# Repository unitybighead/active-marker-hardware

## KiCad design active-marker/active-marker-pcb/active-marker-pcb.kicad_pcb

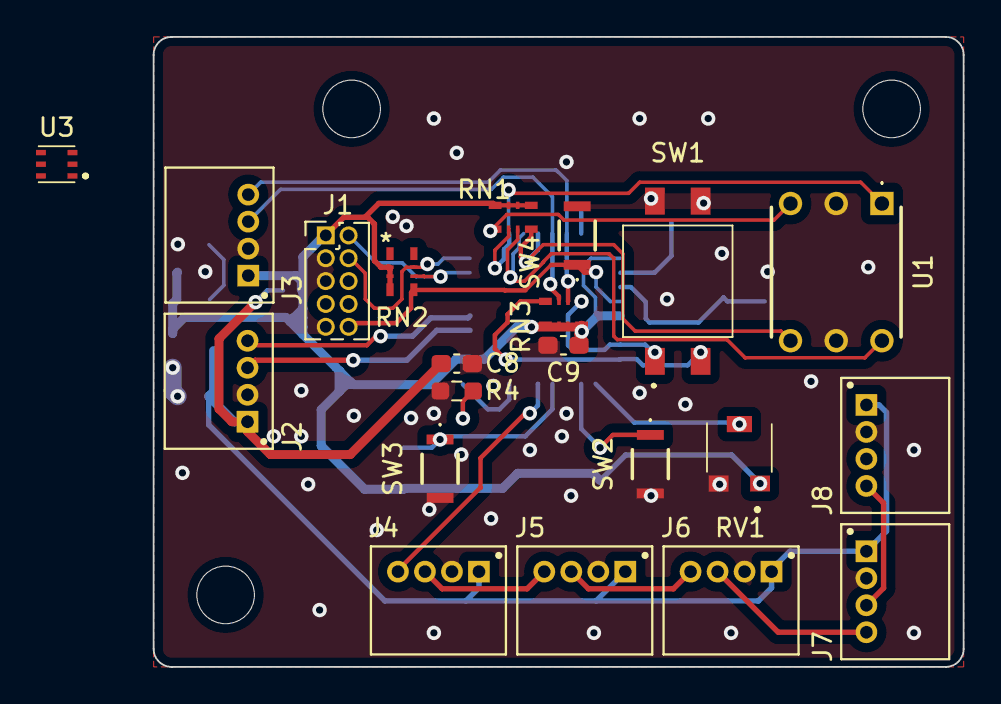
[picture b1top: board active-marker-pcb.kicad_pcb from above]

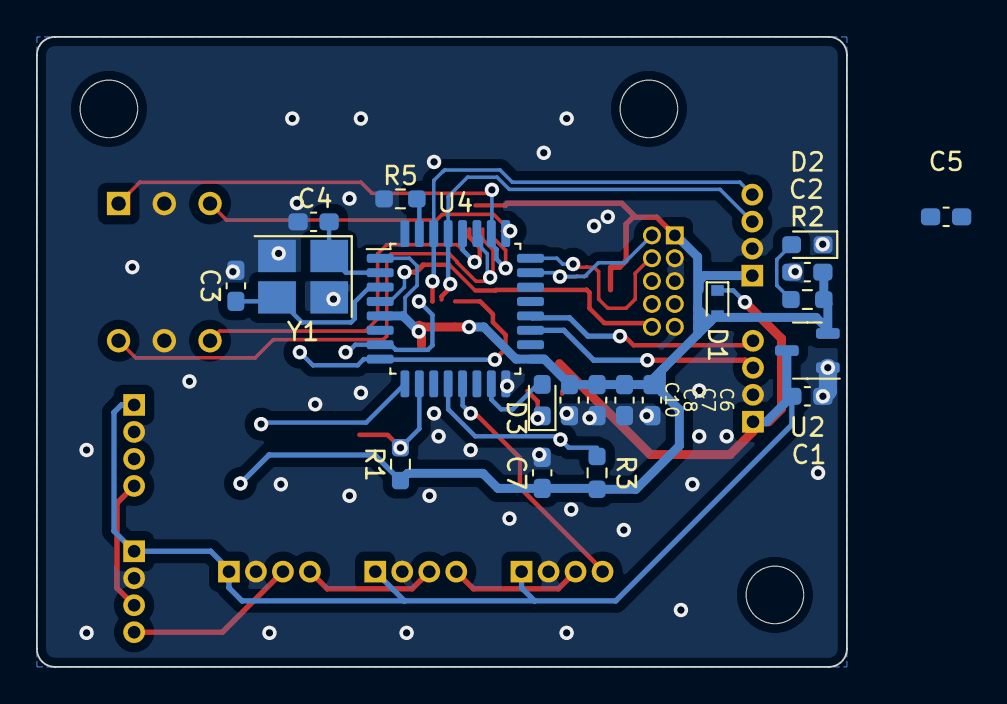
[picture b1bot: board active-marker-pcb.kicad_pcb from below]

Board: 2 copper layers, 45.0 x 35.0 mm, 44 parts (20 on the bottom side), 30 nets.

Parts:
C1, C7#2: 1u; C_0603_1608Metric_Pad1.08x0.95mm_HandSolder
C2: 10u; C_0603_1608Metric_Pad1.08x0.95mm_HandSolder
C3, C4: 15p; C_0603_1608Metric_Pad1.08x0.95mm_HandSolder
C5, C7, C8: 0.1u; C_0603_1608Metric_Pad1.08x0.95mm_HandSolder
C6: 4.7u; C_0603_1608Metric_Pad1.08x0.95mm_HandSolder
C8#2, C9: 100n; C_0603_1608Metric_Pad1.08x0.95mm_HandSolder
C10: 10n; C_0603_1608Metric_Pad1.08x0.95mm_HandSolder
D1: D_Schottky; D_SOD-523
D2: Power; LED_0603_1608Metric_Pad1.05x0.95mm_HandSolder
D3: LED_Small; LED_0603_1608Metric_Pad1.05x0.95mm_HandSolder
H1, H2, H3: MountingHole; MountingHole_3.2mm_M3_ISO7380
J1: Conn_01x10; PinHeader_2x05_P1.27mm_Vertical
J2, J3, J4, J5, J6, J7, J8: Conn_01x04; JST_S4B-ZR_LF__SN_
R1, R3, R5: 10k; R_0603_1608Metric_Pad0.98x0.95mm_HandSolder
R2, R4: 1k; R_0603_1608Metric_Pad0.98x0.95mm_HandSolder
RN1, RN2, RN3: 10k; BO_CAY10_PAN-L
RV1: 10k; PVG3A202C01R00
SW1: SW_DIP_x02; DS04254202BKSMT
SW2, SW3, SW4: SW_Push; EVP6AWD40
U1: 220ADA16
U2: XC6206PxxxMR; SOT-23-3
U3: VEML6030
U4: STM32F303K8Tx; LQFP-32_7x7mm_P0.8mm
Y1: NX3225GA-32M; Crystal_SMD_3225-4Pin_3.2x2.5mm_HandSoldering

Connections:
+3V3: C2.1, C5.1, C6.1, C7.1, C7#2.1, C8#2.1, C9.1, C10.1, D1.2 (A), J1.1, J3.4, R1.1, R2.1, R3.1, RN1.1 (R1.1), RN1.3 (R2.1), RN1.5 (R3.1), RN1.7 (R4.1), RN2.3 (R2.1), RN2.5 (R3.1), RN2.7 (R4.1), RN3.1 (R1.1), RN3.3 (R2.1), RN3.5 (R3.1), RN3.7 (R4.1), RV1.1, U2.2 (VO), U3.4 (ADD), U3.6 (VDD), U4.1 (VDD), U4.5 (VDDA), U4.17 (VDD)
+5V: C1.1, C8.1, D1.1 (K), J2.4, J4.4, J5.4, J6.4, J7.4, J8.4, U2.3 (VI)
/D12: J4.2, J5.1
/D23: J5.2, J6.1
/D34: J6.2, J7.1
/D45: J7.2, J8.1
/I2C_SCL: J3.2, RN3.4 (R2.2), U3.5 (SCL), U4.29 (PB6)
/I2C_SDA: J3.1, RN3.6 (R3.2), U3.2 (SDA), U4.30 (PB7)
/ID1: RN1.6 (R3.2), U1.1, U4.26 (PB3)
/ID2: RN1.2 (R1.2), U1.2, U4.28 (PB5)
/ID4: RN1.8 (R4.2), U1.4, U4.25 (PA15)
/ID8: RN1.4 (R2.2), U1.8, U4.27 (PB4)
/OSC_IN: C4.1, U4.2 (PF0), Y1.1
/OSC_OUT: C3.1, U4.3 (PF1), Y1.3
/SPI_MOSI: J4.1, U4.13 (PA7)
/SWCLK: J1.4, RN2.4 (R2.2), U4.24 (PA14)
/SWDIO: J1.2, RN2.6 (R3.2), U4.23 (PA13)
/UART_RX: J2.1, U4.20 (PA10)
/UART_TX: J2.2, U4.19 (PA9)
/USER_BUTTON1: R1.2, SW2.1, U4.10 (PA4)
/USER_BUTTON2: R3.2, SW3.1, U4.12 (PA6)
/USER_LED: D3.2 (A), U4.15 (PB1)
/USER_SELECT1: RN3.8 (R4.2), SW1.1, U4.7 (PA1)
/USER_SELECT2: RN3.2 (R1.2), SW1.2, U4.8 (PA2)
/USER_VR: RV1.2, U4.9 (PA3)
/~NRST: J1.10, RN2.8 (R4.2), SW4.1, U4.4 (NRST)
GND: C1.2, C2.2, C3.2, C4.2, C5.2, C6.2, C7.2, C7#2.2, C8.2, C8#2.2, C9.2, C10.2, D2.1 (K), J1.3, J1.5, J1.9, J2.3, J3.3, J4.3, J5.3, J6.3, J7.3, J8.3, R4.2, R5.2, RV1.3, SW1.3, SW1.4, SW2.2, SW3.2, SW4.2, U1.C1, U1.C2, U2.1 (GND), U3.1 (GND), U4.16 (VSS), U4.32 (VSS), Y1.2, Y1.4
unnamed: D2.2 (A), R2.2
unnamed: D3.1 (K), R4.1
unnamed: R5.1, U4.31 (BOOT0)

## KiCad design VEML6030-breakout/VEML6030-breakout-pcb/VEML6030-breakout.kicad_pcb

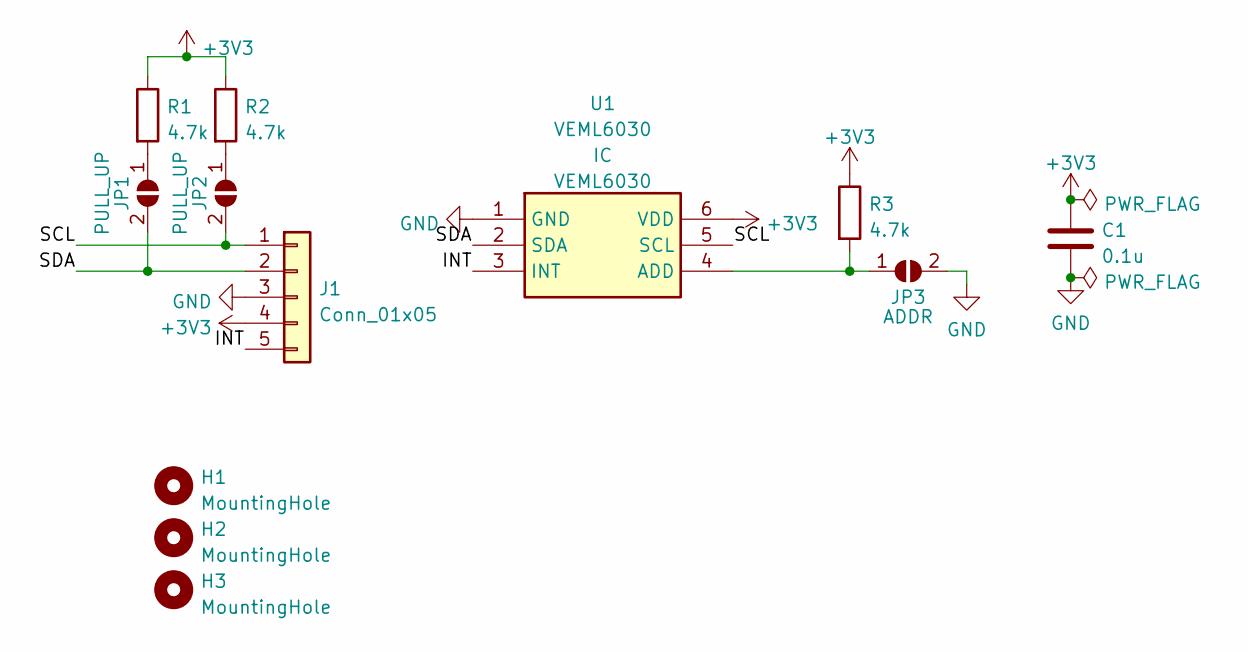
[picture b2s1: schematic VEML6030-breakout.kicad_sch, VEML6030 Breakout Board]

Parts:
C1: 0.1u; C_0603_1608Metric_Pad1.08x0.95mm_HandSolder
H1, H2, H3: MountingHole; MountingHole_3.2mm_M3_ISO7380
J1: Conn_01x05; JST_XH_S5B-XH-A_1x05_P2.50mm_Horizontal
JP1, JP2: PULL_UP; SolderJumper-2_P1.3mm_Open_Pad1.0x1.5mm
JP3: ADDR; SolderJumper-2_P1.3mm_Open_Pad1.0x1.5mm
R1, R2, R3: 4.7k; R_0603_1608Metric_Pad0.98x0.95mm_HandSolder
U1: VEML6030; Mouser Part Number 78-VEML6030

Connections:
+3V3: C1.1, J1.4, R1.1, R2.1, R3.1, U1.6 (VDD)
/INT: J1.5, U1.3 (INT)
/SCL: J1.1, JP2.2 (B), U1.5 (SCL)
/SDA: J1.2, JP1.2 (B), U1.2 (SDA)
GND: C1.2, J1.3, JP3.2 (B), U1.1 (GND)
unnamed: JP1.1 (A), R1.2
unnamed: JP2.1 (A), R2.2
unnamed: JP3.1 (A), R3.2, U1.4 (ADD)

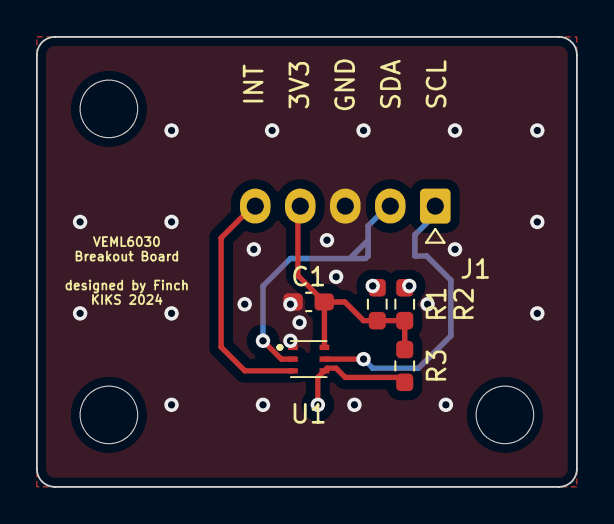
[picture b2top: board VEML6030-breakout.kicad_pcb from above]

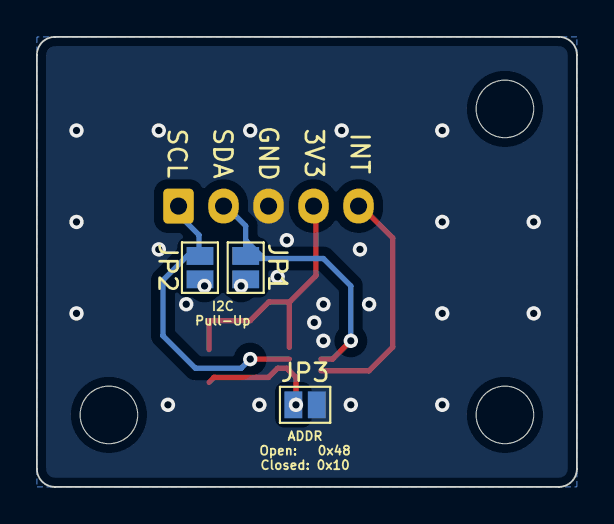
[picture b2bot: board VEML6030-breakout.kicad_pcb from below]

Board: 2 copper layers, 30.0 x 25.0 mm, 12 parts (3 on the bottom side), 8 nets.

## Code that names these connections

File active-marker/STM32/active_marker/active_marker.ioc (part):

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Mcu.Name=STM32F303K(6-8)Tx
Mcu.Package=LQFP32
Mcu.UserName=STM32F303K6Tx
PA1.GPIOParameters=GPIO_Label
PA1.GPIO_Label=MODE
PA1.Signal=GPIO_Input
PA10.Mode=Asynchronous
PA10.Signal=USART1_RX
PA13.Mode=Serial_Wire
PA13.Signal=SYS_JTMS-SWDIO
PA14.Mode=Serial_Wire
PA14.Signal=SYS_JTCK-SWCLK
PA15.GPIOParameters=GPIO_Label
PA15.GPIO_Label=ID4
PA15.Signal=GPIO_Input
PA2.GPIOParameters=GPIO_Label,GPIO_ModeDefaultEXTI
PA2.GPIO_Label=COLOR
PA2.GPIO_ModeDefaultEXTI=GPIO_MODE_IT_RISING_FALLING
PA2.Signal=GPXTI2
PA3.GPIOParameters=GPIO_Label
PA3.GPIO_Label=USER_VR
PA3.Signal=GPIO_Analog
PA4.GPIOParameters=GPIO_Label,GPIO_ModeDefaultEXTI
PA4.GPIO_Label=USER_BTN1
PA4.GPIO_ModeDefaultEXTI=GPIO_MODE_IT_FALLING
PA4.Signal=GPXTI4
PA5.Mode=Simplex_Bidirectional_Master
PA5.Signal=SPI1_SCK
PA6.GPIOParameters=GPIO_Label,GPIO_ModeDefaultEXTI
PA6.GPIO_Label=USER_BTN2
PA6.GPIO_ModeDefaultEXTI=GPIO_MODE_IT_FALLING
PA6.Signal=GPXTI6
PA7.Mode=Simplex_Bidirectional_Master
PA7.Signal=SPI1_MOSI
PA9.Mode=Asynchronous
PA9.Signal=USART1_TX
PB1.GPIOParameters=GPIO_Label
PB1.GPIO_Label=USER_LED
PB1.Signal=GPIO_Output
PB3.GPIOParameters=GPIO_Label,GPIO_ModeDefaultEXTI
PB3.GPIO_Label=ID1
PB3.GPIO_ModeDefaultEXTI=GPIO_MODE_IT_RISING_FALLING
PB3.Signal=GPXTI3
PB4.GPIOParameters=GPIO_Label
PB4.GPIO_Label=ID8
PB4.Signal=GPIO_Input
PB5.GPIOParameters=GPIO_Label,GPIO_ModeDefaultEXTI
PB5.GPIO_Label=ID2
PB5.GPIO_ModeDefaultEXTI=GPIO_MODE_IT_RISING_FALLING
PB5.Signal=GPXTI5
PB6.Mode=I2C
PB6.Signal=I2C1_SCL
PB7.Mode=I2C
PB7.Signal=I2C1_SDA
PF0\ /\ OSC_IN.Mode=HSE-External-Oscillator
PF0\ /\ OSC_IN.Signal=RCC_OSC_IN
PF1\ /\ OSC_OUT.Mode=HSE-External-Oscillator
PF1\ /\ OSC_OUT.Signal=RCC_OSC_OUT
RCC.HSEPLLFreq_Value=4000000
RCC.HSE_VALUE=32000000
RCC.SYSCLKFreq_VALUE=52000000
RCC.SYSCLKSourceVirtual=RCC_SYSCLKSOURCE_PLLCLK
board=custom

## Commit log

2024-05-09 add VEML6030 breakout board
2024-05-16 add gerber files
2024-05-16 add active-marker mother board pcb
2024-05-16 fix Pinmap and add some vias
2024-05-16 plot gerber file
2024-05-16 add LED-module
2024-05-16 add diode, fix gerber files
2024-05-16 add gitignore
2024-05-18 fix a placement of mounting hole
2024-05-18 fix pinmap of ZH4 connector
2024-05-23 add VEML6030 testing sketch for M5StickC
2024-05-23 add STM32 files
    auto-generated files will be managed
2024-05-27 add some libraries
    VEML6030.h and user_func.h
2024-05-30 add VEML6030_test and fix library
2024-06-14 add neopixel_test, active_marker
2024-06-19 fixed spi settings and it can be used as marker
2024-07-22 add 1655 module (bigger)
2024-08-01 M5StickCにudp機能を追加
2024-08-05 fix pattern
2024-08-05 fix set_color
2024-08-05 UARTに対応させた 要デバッグ
2024-08-05 spiのNSSPが勝手に変わっていた
2024-08-06 Illuminaceのデータを受け取れるように
2024-08-08 colorの処理を変更
2024-08-20 ボタン等に割り込み対応
2024-08-21 add LED matrix
2024-08-23 add clearance
2024-09-21 uart信号が正常に届かない場合リセットを掛ける
2024-09-21 uartを高速化、その他動作の安定化を図る
2024-09-21 add stamphole
2024-11-05 brkoutを修正
2024-11-06 外付け照度センサを有効化
2024-11-11 expand
2024-11-17 add interbal
2024-11-28 set default config
2024-12-09 add demo
2025-02-01 rename 3484
2025-02-01 rename center single
2025-02-01 add side
2025-02-01 add led module list
2025-02-01 rename outer
2025-02-01 add .step
2025-02-01 replace .step
2025-03-08 update default value
